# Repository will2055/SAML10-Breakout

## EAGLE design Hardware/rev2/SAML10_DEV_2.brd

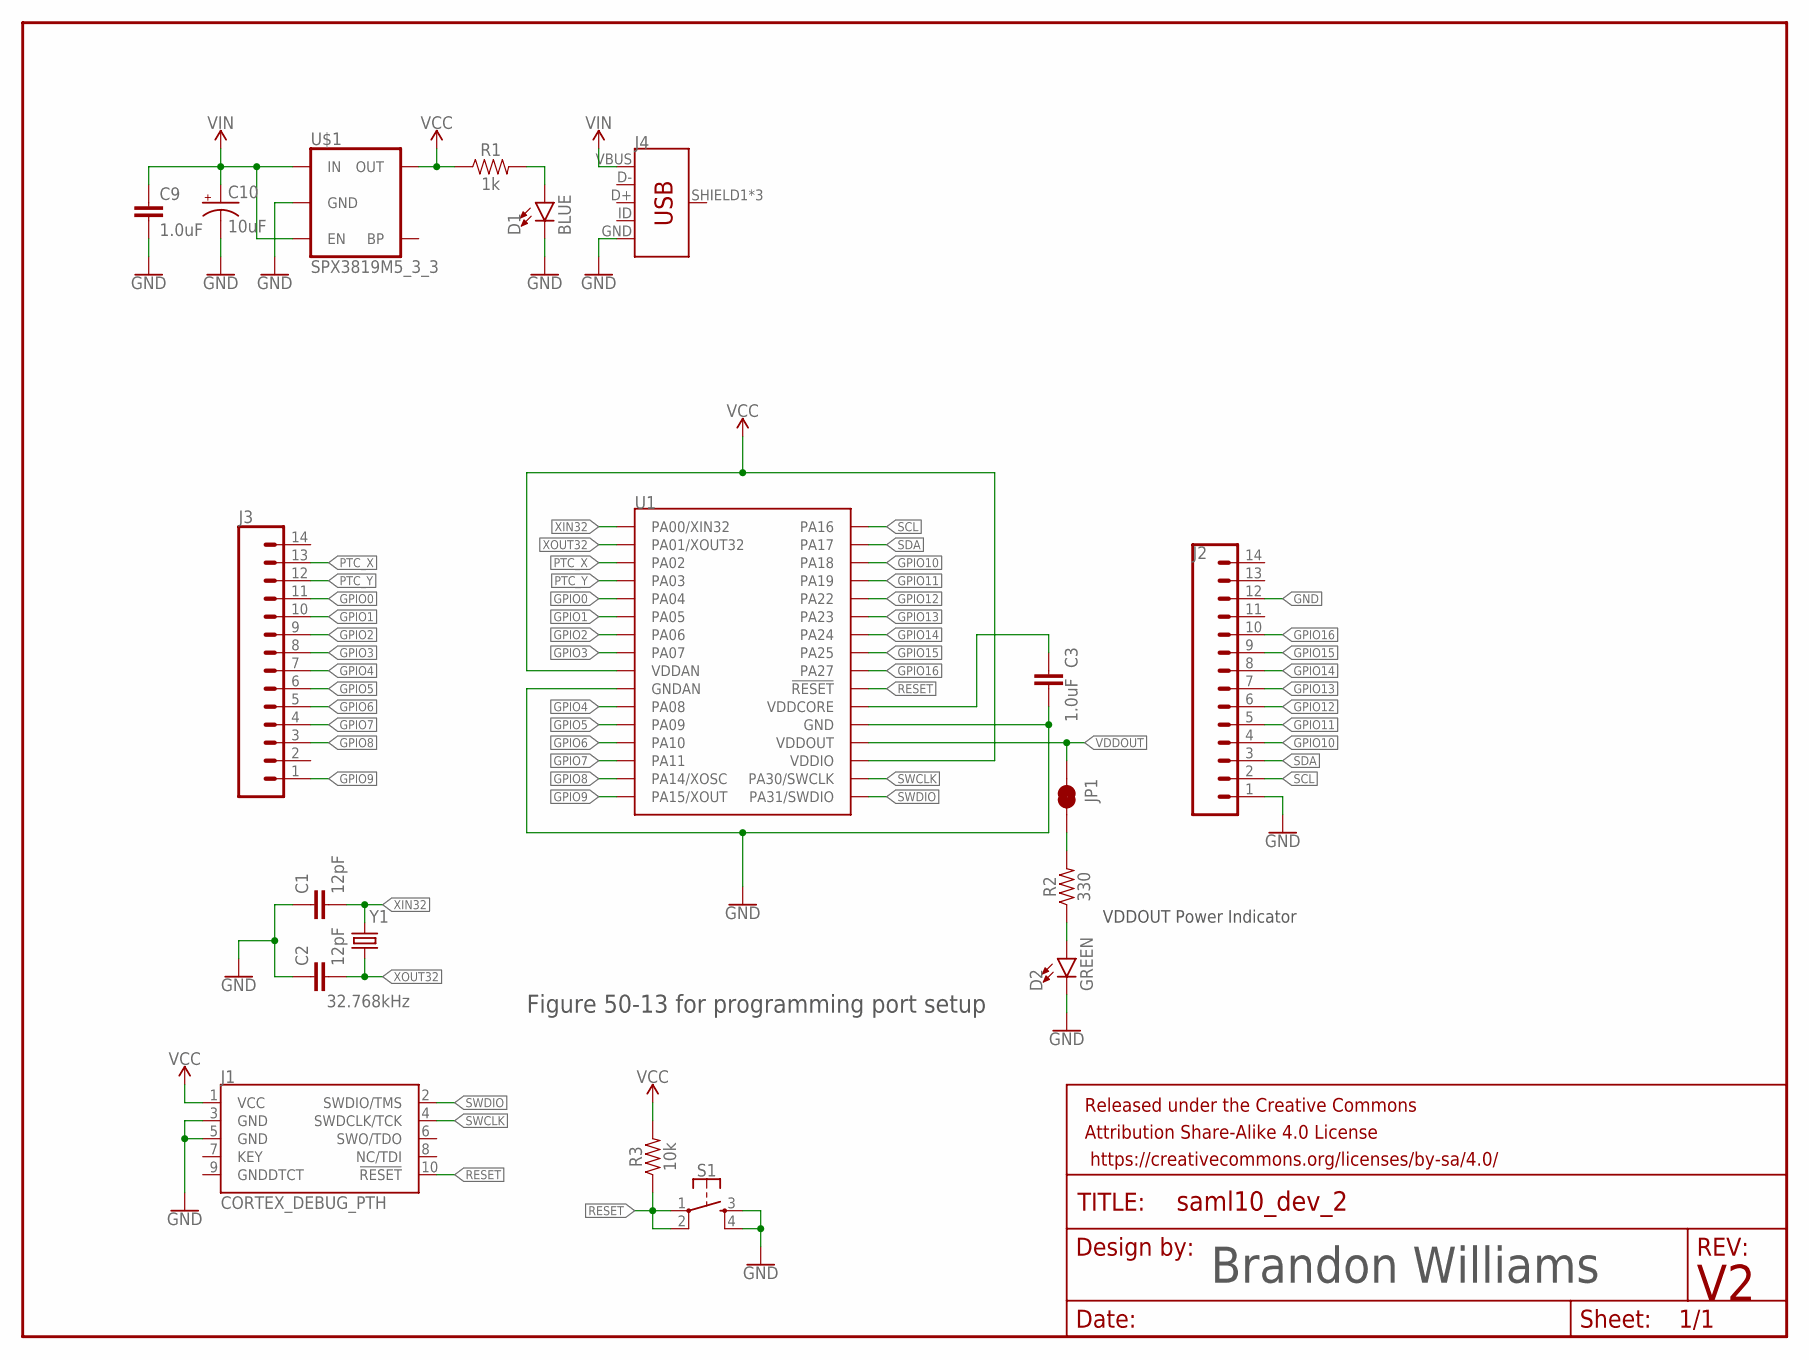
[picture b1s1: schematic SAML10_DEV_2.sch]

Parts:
C1, C2: 12pF; 0603
C3: 1.0uF; 0603
C9: 1.0uF; 0402
C10: 10uF; 0603-POLAR
D1: BLUE; LED-0603
D2: GREEN; LED-0603
FRAME1: FRAME-LETTERNO_PACKAGE; DUMMY
J1: CORTEX_DEBUG_PTH; 2X5-PTH-1.27MM
J2, J3: CONN_14; 1X14
J4: USB_MICRO-BREDUCED_PASTE; USB-B-MICRO-SMD_RED_PASTE
JP1: JUMPER-SMT_2_NC_TRACE_NO-SILK; SMT-JUMPER_2_NC_TRACE_NO-SILK
R1: 1k; 0603
R2: 330; 0603
R3: 10k; 0603
S1: MOMENTARY-SWITCH-SPST-2-SMD-4.6X2.8MM; TACTILE_SWITCH_SMD_4.6X2.8MM
U1: SAML10; ATSAML10E15A-MU-ND
U$1: SPX3819M5_3_3; SOT23-5
Y1: 32.768kHz; CRYSTAL-SMD-3.2X1.5MM

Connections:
GND: C1.1, C2.1, C3.2, C9.2, C10.-, D1.C, D2.C, J1.3 (GND), J1.5 (GND), J2.1, J2.12, J4.GND, S1.3, S1.4, U1.P$10 (GNDAN), U1.P$28 (GND), U$1.2 (GND)
GPIO0: J3.11, U1.P$5 (PA04)
GPIO1: J3.10, U1.P$6 (PA05)
GPIO2: J3.9, U1.P$7 (PA06)
GPIO3: J3.8, U1.P$8 (PA07)
GPIO4: J3.7, U1.P$11 (PA08)
GPIO5: J3.6, U1.P$12 (PA09)
GPIO6: J3.5, U1.P$13 (PA10)
GPIO7: J3.4, U1.P$14 (PA11)
GPIO8: J3.3, U1.P$15 (PA14/XOSC)
GPIO9: J3.1, U1.P$16 (PA15/XOUT)
GPIO10: J2.4, U1.P$19 (PA18)
GPIO11: J2.5, U1.P$20 (PA19)
GPIO12: J2.6, U1.P$21 (PA22)
GPIO13: J2.7, U1.P$22 (PA23)
GPIO14: J2.8, U1.P$23 (PA24)
GPIO15: J2.9, U1.P$24 (PA25)
GPIO16: J2.10, U1.P$25 (PA27)
unnamed: JP1.2, R2.2
unnamed: D2.A, R2.1
unnamed: C3.1, U1.P$27 (VDDCORE)
unnamed: D1.A, R1.2
PTC_X: J3.13, U1.P$3 (PA02)
PTC_Y: J3.12, U1.P$4 (PA03)
RESET: J1.10 (!RESET), R3.1, S1.1, S1.2, U1.P$26 (!RESET)
SCL: J2.2, U1.P$17 (PA16)
SDA: J2.3, U1.P$18 (PA17)
SWCLK: J1.4 (SWDCLK/TCK), U1.P$31 (PA30/SWCLK)
SWDIO: J1.2 (SWDIO/TMS), U1.P$32 (PA31/SWDIO)
VCC: J1.1 (VCC), R1.1, R3.2, U1.P$9 (VDDAN), U1.P$30 (VDDIO), U$1.5 (OUT)
VDDOUT: JP1.1, U1.P$29 (VDDOUT)
VIN: C9.1, C10.+, J4.VBUS, U$1.1 (IN), U$1.3 (EN)
XIN32: C1.2, U1.P$1 (PA00/XIN32), Y1.P$1 (1)
XOUT32: C2.2, U1.P$2 (PA01/XOUT32), Y1.P$2 (2)

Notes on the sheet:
Figure 50-13 for programming port setup
VDDOUT Power Indicator
Brandon Williams

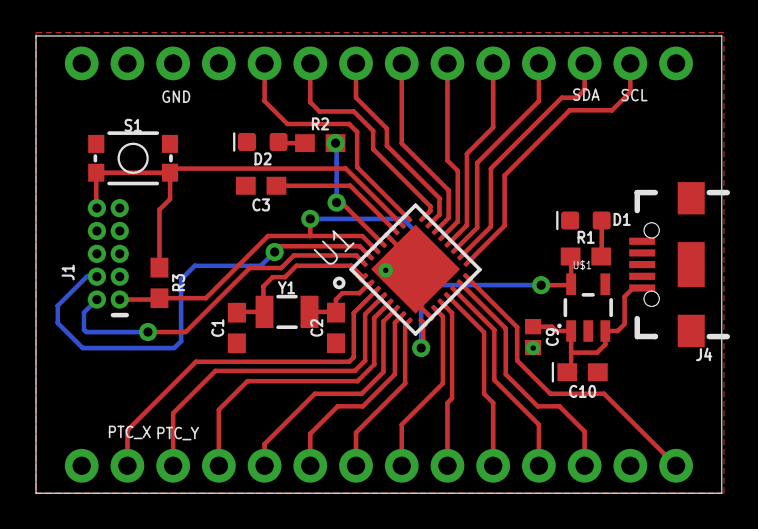
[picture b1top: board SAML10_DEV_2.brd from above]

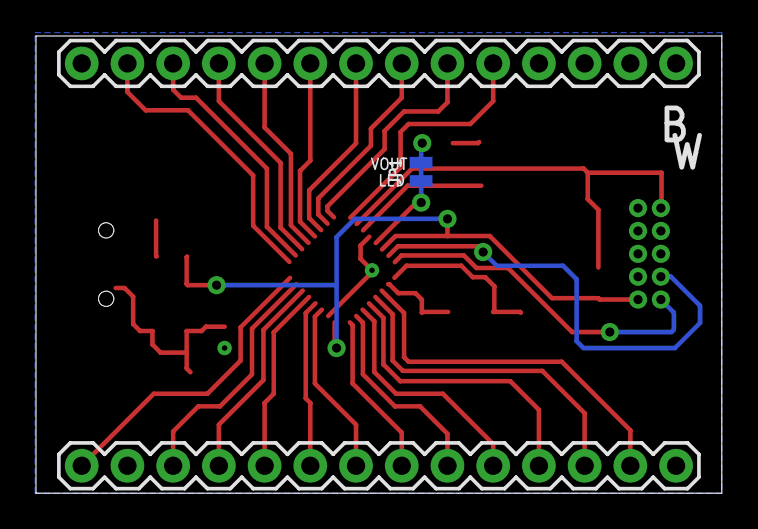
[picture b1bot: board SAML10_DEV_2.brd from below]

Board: 2 copper layers, 38.1 x 25.4 mm, 20 parts (3 on the bottom side), 34 nets.

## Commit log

2020-01-13 create hardware/readme
2020-01-13 upload eagle files
2020-01-13 create eagle part libraries folder
2020-01-13 upload ARM-Cortex-23 eagle part library
2020-01-14 make rev_1 folder, move old files to rev_1
    There are several wiring issues that need to be addressed.
2020-01-27 Power Routing Fixes 1
2020-01-28 power pins fixed, added reset switch
    RESET active LOW, pulled RESET High by default
2020-02-05 final rev2 files
    move to prototype production
2020-02-24 Rev 2 Board Design Updates
    Fixed lack of power connections to IC. Rotated SWD connector for better connection. Trimmed other "needless" parts for the meantime. Keepin' it lean.
2020-07-05 Swapped RESET pull up
    from 4.7K to 10K

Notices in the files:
parts and their libraries:
SparkFun-Capacitors: Licensing: Creative Commons ShareAlike 4.0 International - https://creativecommons.org/licenses/by-sa/4.0
SparkFun-Aesthetics: Released under the Creative Commons Attribution Share-Alike 4.0 License
SparkFun-Aesthetics: https://creativecommons.org/licenses/by-sa/4.0
